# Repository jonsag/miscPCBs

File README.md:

# miscPCBs

A collection of own designed PCBs.  

## 2PinLCDBackPack

Interface and Arduino to an HD4470 LCD using the I2C protocol.  
Uses an PCF8574 I2C I/O bus expander.  

## 3PinLCDBackpack

Interface an Arduino to an HD4470 LCD with 3 pins instead of 6.  
Using the 74HC595 8-bit shift register with output latches.  

## 8PinLCDBackPack

## FM-Transmitter

A miniaturized FM transmitter.  

## LCDBackPack

The default way to control the HD4470 LCD.  

## medzik TDA2005 Amplifier

A basic amplifier using the 2-channel TDA2005.  

## rotaryToolMotorController

Schematics of a Dremel 3000 motor control.  

## TDA2005-amplifiers

1-channel bridged amplifier using TDA2005.  
2-channel amplifier with tone, balance and loudness control. Also with TDA2005.  

## TDA2005R

An amplifier with PCB layout possible to etch at home.  
Uses TDA2005.  

## Uber I2C LCD Controller Module

Even more control over the LCD.

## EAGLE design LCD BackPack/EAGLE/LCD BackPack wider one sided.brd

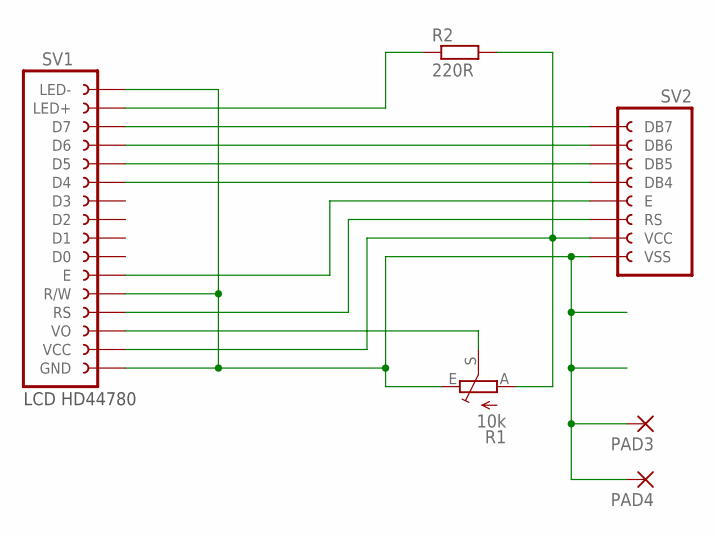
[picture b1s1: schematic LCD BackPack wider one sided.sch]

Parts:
PAD3, PAD4: 1,6/0,8
R1: 10k; CA6V
R2: 220R; 0204/7
SV1: LCD-HD44780-16-PIN_FEMALE_HEADER
SV2: LCD-CONTROL_8-PIN_FEMALE_HEADER

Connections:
DB4: SV1.D4, SV2.DB4
DB5: SV1.D5, SV2.DB5
DB6: SV1.D6, SV2.DB6
DB7: SV1.D7, SV2.DB7
E: SV1.E, SV2.E
GND: PAD3.1, PAD4.1, R1.E, SV1.GND, SV1.LED-, SV1.R/W, SV2.VSS
LED+: R2.1, SV1.LED+
unnamed: R1.S, SV1.VO
RS: SV1.RS, SV2.RS
VCC: R1.A, R2.2, SV1.VCC, SV2.VCC

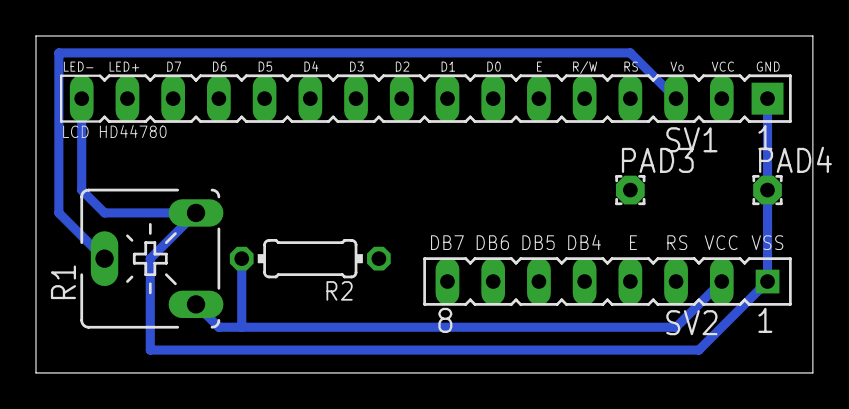
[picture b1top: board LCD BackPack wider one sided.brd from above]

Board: 2 copper layers, 43.2 x 18.7 mm, 6 parts (0 on the bottom side), 10 nets.

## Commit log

2020-02-03 added LCD BackPack
2020-02-08 added KiCad
2020-02-08 copper pour
2020-02-15 added 3 pin LCD
2020-03-07 new layout
2020-05-10 added TDA2005R amplifier
2020-05-10 larger pads
2020-05-10 wider tracks and text
2020-05-12 new component sizes
2020-05-13 new resistors, new heatsink
2020-05-17 new amplifiers
2020-05-17 new potentiometers
2021-09-27 3 pin LCD
2021-09-27 LiquidCrystal595 arduino library
2021-09-28 ESP-programmer
2021-12-27 new switches, better 3d
2022-05-17 3 pin lcd backpack, new pcb
2022-05-17 esp-01 programmer board
2022-05-17 kicad6
2022-05-18 amplifier
2022-05-18 deletions
2022-05-18 bridged amplifier
2022-05-18 2-channel
2022-05-18 3-pin
2022-06-10 3pinLCD
2022-06-11 new pcb for 3pinlcd
2022-06-11 rotary tool
2022-06-11 readded LCD backpack
2022-06-11 new sketch
2022-06-11 lcd backpack
2022-06-12 ESPxxProgrammer
2022-09-01 8-pin LCD
2022-10-23 moved to another git
2022-10-30 fm transmitter
2025-02-01 revision
2025-02-01 cleaning and revising
2025-02-02 more revisions
2025-02-03 UBER LCD Control
2025-02-06 IR receiver
2025-02-07 RPi IR
